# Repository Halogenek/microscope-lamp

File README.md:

# Microscope Lamp
Lightning is key in photography. I started to do extreme electronics macrophotography using a 4X microscope objective: [(blog post)](https://niemczuk.tech/2024/02/11/detailed-macrophotography-of-PCBs), but the photographs had low contrast and shadows. So I created this little USB-C powered LED fixture that fits on top of the microscope objective and illuminates the scene.
All files (PCB, 3D housing, BOM) are in the repository files. Feel free to build your own.

</br>

 <p xmlns:cc="http://creativecommons.org/ns#" xmlns:dct="http://purl.org/dc/terms/"><span property="dct:title">Microscope Lamp</span> by <a rel="cc:attributionURL dct:creator" property="cc:attributionName" href="https://niemczuk.tech">Jakub Niemczuk</a> is licensed under <a href="http://creativecommons.org/licenses/by-nc-sa/4.0/?ref=chooser-v1" target="_blank" rel="license noopener noreferrer" style="display:inline-block;">CC BY-NC-SA 4.0</a></p>

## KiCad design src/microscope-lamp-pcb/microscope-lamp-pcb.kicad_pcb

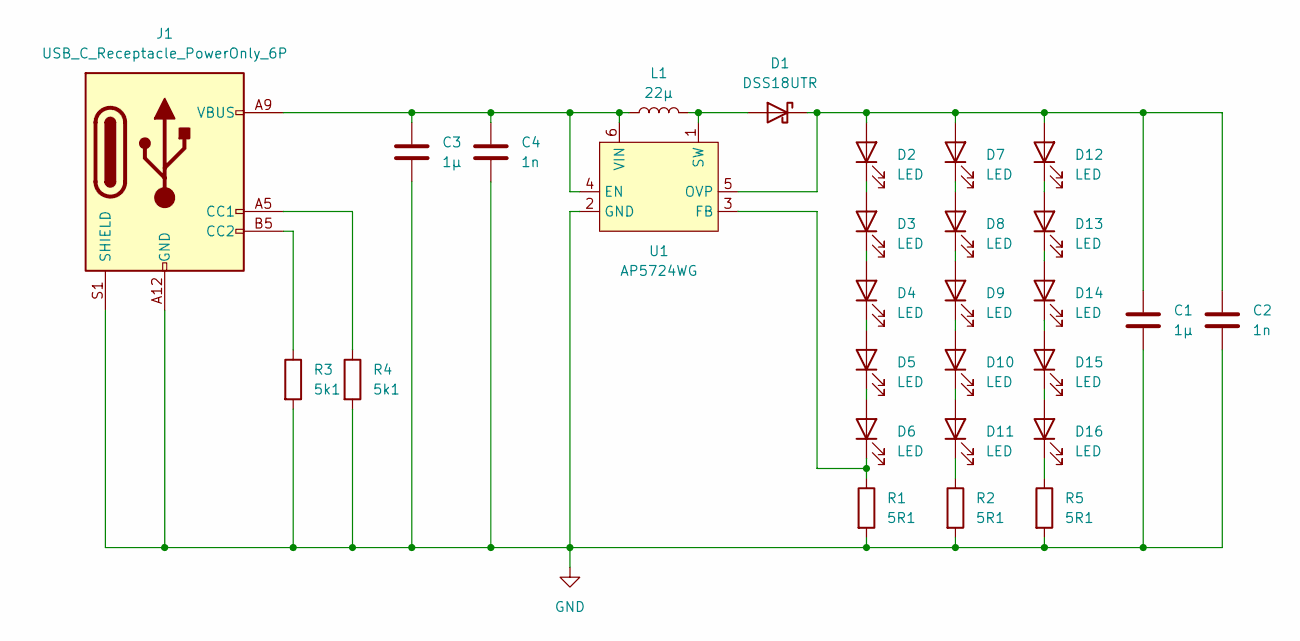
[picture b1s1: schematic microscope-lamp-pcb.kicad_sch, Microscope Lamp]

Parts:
C1, C3: 1µ; C_0603_1608Metric
C2, C4: 1n; C_0603_1608Metric
D1: DSS18UTR; D_SOD-123F
D2, D3, D4, D5, D6, D7, D8, D9, D10, D11, D12, D13, D14, D15, D16: LED; LED_D3.0mm
J1: USB_C_Receptacle_PowerOnly_6P; USB_C_Receptacle_GCT_USB4135-GF-A_6P_TopMnt_Horizontal
L1: 22µ; L_Taiyo-Yuden_NR-30xx
R1, R2, R5: 5R1; R_0603_1608Metric
R3, R4: 5k1; R_0603_1608Metric
U1: AP5724WG; TSOT-23-6

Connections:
GND: C1.2, C2.2, C3.2, C4.2, J1.A12 (GND), J1.B12 (GND), J1.S1 (SHIELD), R1.2, R2.2, R3.2, R4.2, R5.2, U1.2 (GND)
unnamed: D1.2 (A), L1.2, U1.1 (SW)
unnamed: C1.1, C2.1, D1.1 (K), D2.2 (A), D7.2 (A), D12.2 (A), U1.5 (OVP)
unnamed: D2.1 (K), D3.2 (A)
unnamed: D3.1 (K), D4.2 (A)
unnamed: D4.1 (K), D5.2 (A)
unnamed: D5.1 (K), D6.2 (A)
unnamed: D6.1 (K), R1.1, U1.3 (FB)
unnamed: D7.1 (K), D8.2 (A)
unnamed: D8.1 (K), D9.2 (A)
unnamed: D9.1 (K), D10.2 (A)
unnamed: D10.1 (K), D11.2 (A)
unnamed: D11.1 (K), R2.1
unnamed: D12.1 (K), D13.2 (A)
unnamed: D13.1 (K), D14.2 (A)
unnamed: D14.1 (K), D15.2 (A)
unnamed: D15.1 (K), D16.2 (A)
unnamed: D16.1 (K), R5.1
unnamed: J1.A5 (CC1), R4.1
unnamed: J1.B5 (CC2), R3.1
unnamed: C3.1, C4.1, J1.A9 (VBUS), J1.B9 (VBUS), L1.1, U1.4 (EN), U1.6 (VIN)

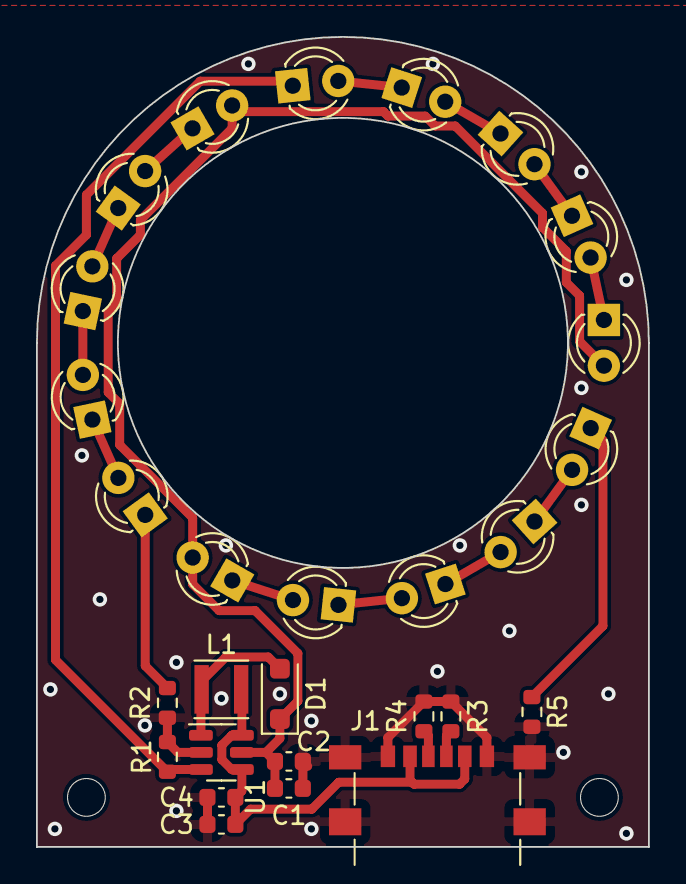
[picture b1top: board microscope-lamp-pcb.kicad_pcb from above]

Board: 2 copper layers, 34.0 x 45.0 mm, 30 parts (0 on the bottom side), 21 nets.

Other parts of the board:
H1, H2: MountingHole_2.1mm

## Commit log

2024-02-04 Initial commit.
    Creating schematic and PCB.
2024-02-04 Adding 3D printed enclosure
2024-02-18 Updating component info.
2024-02-27 changing 3D housing
2024-03-03 adding photos of the lamp and licensing information prior publishing on github
2024-03-17 removing OSH logo
